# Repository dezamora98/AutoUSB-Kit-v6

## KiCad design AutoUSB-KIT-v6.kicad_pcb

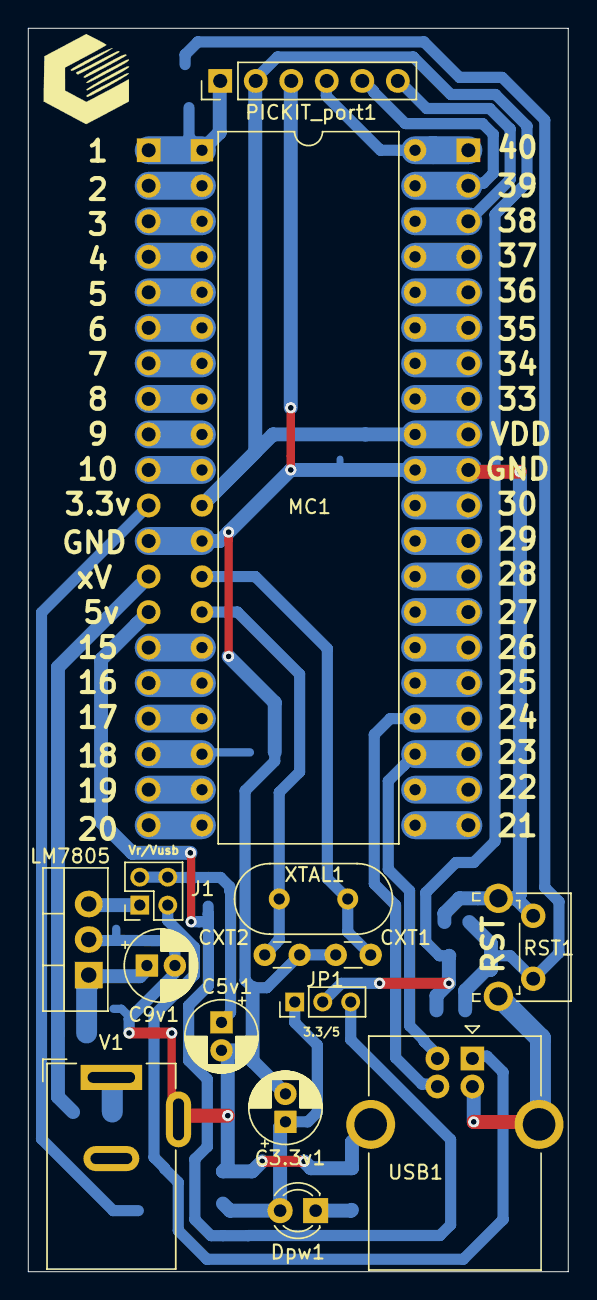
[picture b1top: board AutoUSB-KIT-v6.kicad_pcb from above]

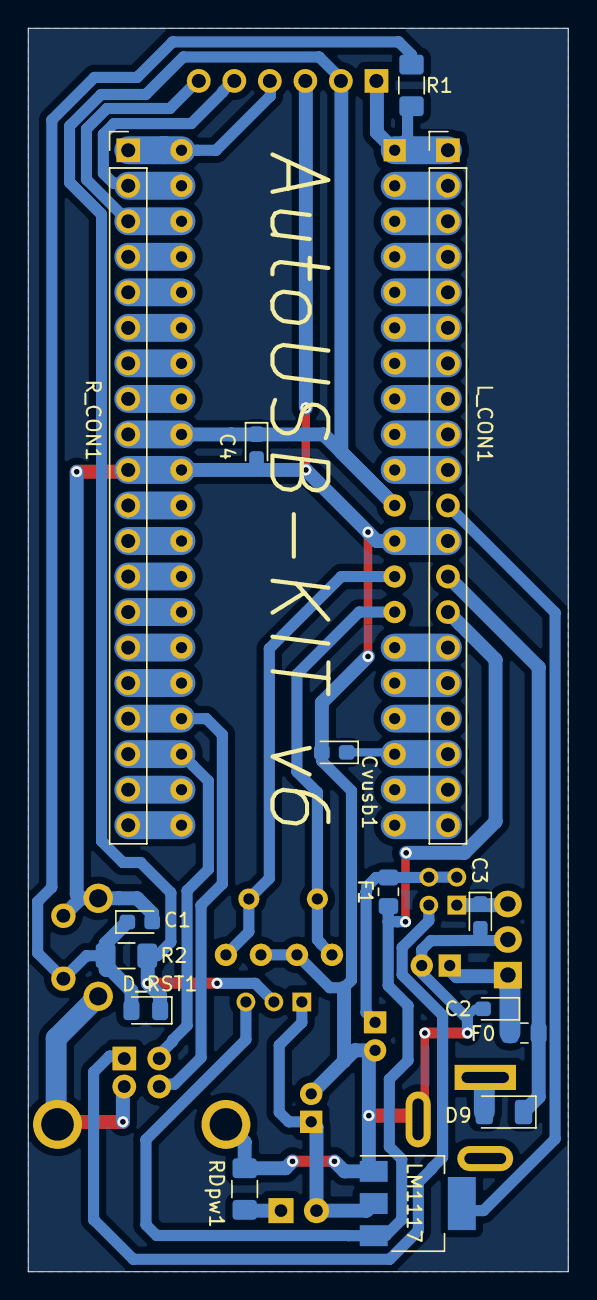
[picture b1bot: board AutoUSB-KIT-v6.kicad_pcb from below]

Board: 2 copper layers, 38.6 x 88.9 mm, 30 parts (15 on the bottom side), 47 nets.

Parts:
C1: 10u; CP_EIA-2012-12_Kemet-R
C2, C3, C4: 0.1u; CP_EIA-2012-12_Kemet-R
C3.3v1, C5v1: 47u; CP_Radial_D5.0mm_P2.00mm
C9v1: 100u; CP_Radial_D5.0mm_P2.00mm
CXT1, CXT2: 15pF; C_Disc_D3.0mm_W1.6mm_P2.50mm
Cvusb1: 0.1u; CP_EIA-2012-12_Kemet-R
D9: D; D_1206_3216Metric
D_RST1: D; D_0805_2012Metric_Pad1.15x1.40mm_HandSolder
Dpw1: LED; LED_D3.0mm
F0: 1A; Fuse_0805_2012Metric_Pad1.15x1.40mm_HandSolder
F1: 200mA; Fuse_0805_2012Metric_Pad1.15x1.40mm_HandSolder
J1: Conn_02x02_Odd_Even; PinHeader_2x02_P2.00mm_Vertical
JP1: 3.3/5; PinHeader_1x03_P2.00mm_Vertical
LM1117: AP1117-15; SOT-223-3_TabPin2
LM7805: L7805; TO-220-3_Vertical
L_CON1: Conn_01x20_Male; PinHeader_1x20_P2.54mm_Vertical
MC1: PIC18F4550-IP; DIP-40_W15.24mm
PICKIT_port1: PICKIT_port; PinHeader_1x06_P2.54mm_Vertical
R1, R2: 5K; R_1206_3216Metric_Pad1.42x1.75mm_HandSolder
RDpw1: 100; R_1206_3216Metric_Pad1.42x1.75mm_HandSolder
RST1: BT; SW_Tactile_SPST_Angled_PTS645Vx39-2LFS
R_CON1: Conn_01x20_Male; PinHeader_1x20_P2.54mm_Vertical
USB1: USB_B; USB_B_OST_USB-B1HSxx_Horizontal
V1: Jack-DC; BarrelJack_Wuerth_6941xx301002
XTAL1: 20MHz; Crystal_HC18-U_Vertical

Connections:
+3V3: C3.3v1.1, Dpw1.2, JP1.1, LM1117.2, L_CON1.11
+5V: F1.1, JP1.3, LM1117.3, L_CON1.14
AD0: L_CON1.2, MC1.2
AD1: L_CON1.3, MC1.3
AD2_Vref-: L_CON1.4, MC1.4
AD3_Vref+: L_CON1.5, MC1.5
AD4_C2-OUT: L_CON1.7, MC1.7
AD5_CLK1SPP: L_CON1.8, MC1.8
AD6_CLK2SPP: L_CON1.9, MC1.9
AD7_OESPP: L_CON1.10, MC1.10
AD8_INT2: MC1.35, R_CON1.6
AD9_CCP2: MC1.36, R_CON1.5
AD10_INT1_SCK_SCL: MC1.34, R_CON1.7
AD11_KBI0_CSSPP: MC1.37, R_CON1.4
AD12_INT0_SDI_SDA: MC1.33, R_CON1.8
CCP2_T1-IN: L_CON1.16, MC1.16
D+: MC1.24, R_CON1.17, USB1.3
D-: MC1.23, R_CON1.18, USB1.2
GND: C1.2, C2.2, C3.2, C3.3v1.2, C4.2, C5v1.2, C9v1.2, CXT1.2, CXT2.1, Cvusb1.2, LM1117.1, LM7805.2, L_CON1.12, MC1.12, MC1.31, PICKIT_port1.3, RDpw1.2, RST1.1, R_CON1.10, USB1.4, USB1.5, V1.2
KBI1_PGM: MC1.38, PICKIT_port1.6, R_CON1.3
KBI2_PGC: MC1.39, PICKIT_port1.5, R_CON1.2
KBI3_PGD: MC1.40, PICKIT_port1.4, R_CON1.1
unnamed: C1.1, D_RST1.2, R1.2, R2.2, RST1.2
unnamed: C3.1, J1.1, LM7805.3
unnamed: C5v1.1, F1.2, J1.2, J1.4
unnamed: D9.2, V1.1
unnamed: Dpw1.1, RDpw1.1
unnamed: J1.3, USB1.1
OC1: CXT1.1, MC1.13, XTAL1.2
OC2: CXT2.2, MC1.14, XTAL1.1
P1A_CCP1: L_CON1.17, MC1.17
RX_SDO_DT: MC1.26, R_CON1.15
SPP0: L_CON1.19, MC1.19
SPP1: L_CON1.20, MC1.20
SPP2: MC1.21, R_CON1.20
SPP3: MC1.22, R_CON1.19
SPP4: MC1.27, R_CON1.14
SPP5_P1B: MC1.28, R_CON1.13
SPP6_P1C: MC1.29, R_CON1.12
SPP7_P1D: MC1.30, R_CON1.11
T0-IN_C1-OUT: L_CON1.6, MC1.6
T1-OUT_T3-IN: L_CON1.15, MC1.15
TX: MC1.25, R_CON1.16
VCC: C2.1, C9v1.1, D9.1, LM7805.1, L_CON1.13
VDD: C4.1, D_RST1.1, JP1.2, MC1.11, MC1.32, PICKIT_port1.2, R2.1, R_CON1.9
VPP: L_CON1.1, MC1.1, PICKIT_port1.1, R1.1
Vusb_m: Cvusb1.1, L_CON1.18, MC1.18

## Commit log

2023-11-13 add readme
